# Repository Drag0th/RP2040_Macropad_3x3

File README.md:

# RP2040_Macropad_3x3
RP2040_Macropad_3x3 is a compact macropad project designed as a customizable USB input device for productivity and control tasks. It provides a 3×3 key layout combined with three rotary encoders and an integrated display, allowing users to trigger shortcuts, control values, and receive visual feedback in real time. The device is intended for use cases such as workflow automation, media control, creative software, or development environments. Overall, the project serves as a flexible platform for building a dedicated control pad tailored to specific user needs.

# :floppy_disk: Firmware
The RP2040_Macropad_3x3 uses [**QMK firmware**](https://github.com/qmk) as its dedicated software platform, allowing full customization of keys, rotary encoders, and the integrated display. This enables users to configure the macropad for shortcuts, macros, and workflow-specific controls.

# :file_folder: References, Links and Notes
- [RP2040 Datasheet](https://github.com/Drag0th/RP2040_Macropad_3x3/blob/main/Documentation/RP-008371-DS-1-rp2040-datasheet.pdf)
- [W25Q16JV Datasheet](https://github.com/Drag0th/RP2040_Macropad_3x3/blob/main/Documentation/w25q16jv%20spi%20revg%2003222018%20plus.pdf)

# :page_facing_up: License
*All hardware designs are released under the CERN-OHL-P v2 license.*

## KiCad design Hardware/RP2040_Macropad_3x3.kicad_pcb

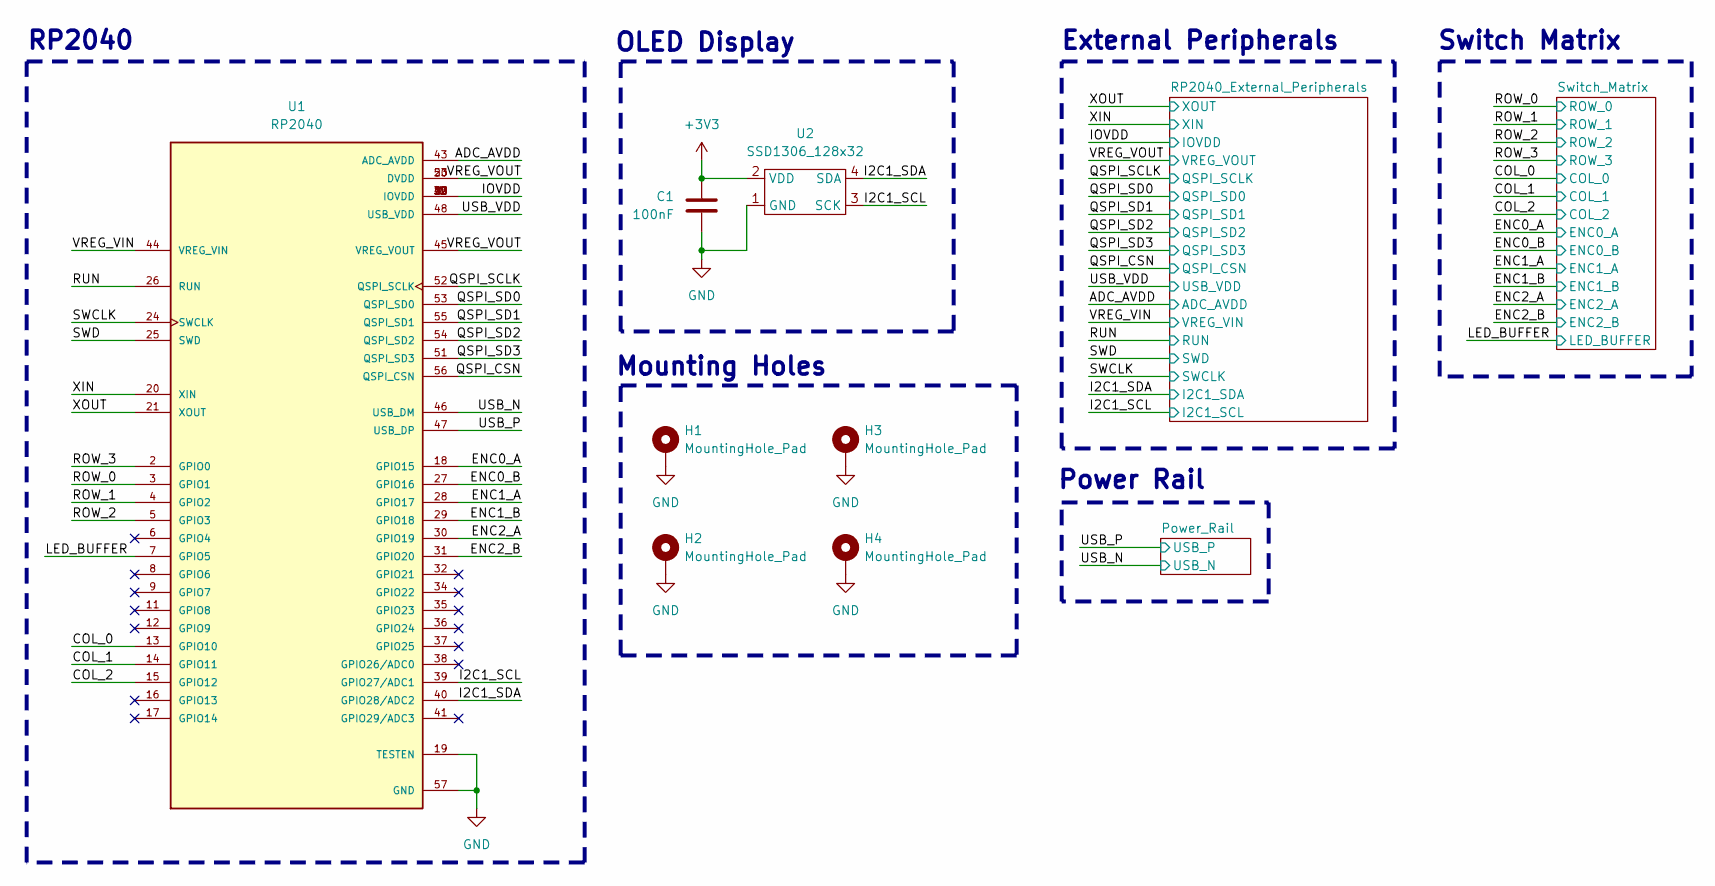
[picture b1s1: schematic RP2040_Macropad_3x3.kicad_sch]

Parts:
C1: 100nF; C_0603_1608Metric_Pad1.08x0.95mm_HandSolder
H1, H2, H3, H4: MountingHole_Pad; MountingHole_3.2mm_M3_Pad
U1: RP2040; QFN40P700X700X90-57N; PARTREV 1.6.1
U2: SSD1306_128x32; SSD1306_128x32_Display_Module

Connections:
+3V3: C1.2, U1.1 (IOVDD), U1.10 (IOVDD), U1.22 (IOVDD), U1.33 (IOVDD), U1.42 (IOVDD), U1.44 (VREG_VIN), U1.48 (USB_VDD), U1.49 (IOVDD), U2.2 (VDD); also elsewhere on the board
/ADC_AVDD: U1.43 (ADC_AVDD); also elsewhere on the board
/COL_0: U1.13 (GPIO10); also elsewhere on the board
/COL_1: U1.14 (GPIO11); also elsewhere on the board
/COL_2: U1.15 (GPIO12); also elsewhere on the board
/ENC0_A: U1.18 (GPIO15); also elsewhere on the board
/ENC0_B: U1.27 (GPIO16); also elsewhere on the board
/ENC1_A: U1.28 (GPIO17); also elsewhere on the board
/ENC1_B: U1.29 (GPIO18); also elsewhere on the board
/ENC2_A: U1.30 (GPIO19); also elsewhere on the board
/ENC2_B: U1.31 (GPIO20); also elsewhere on the board
/I2C1_SCL: U1.39 (GPIO27/ADC1), U2.3 (SCK); also elsewhere on the board
/I2C1_SDA: U1.40 (GPIO28/ADC2), U2.4 (SDA); also elsewhere on the board
/LED_BUFFER: U1.7 (GPIO5); also elsewhere on the board
/QSPI_CSN: U1.56 (QSPI_CSN); also elsewhere on the board
/QSPI_SCLK: U1.52 (QSPI_SCLK); also elsewhere on the board
/QSPI_SD0: U1.53 (QSPI_SD0); also elsewhere on the board
/QSPI_SD1: U1.55 (QSPI_SD1); also elsewhere on the board
/QSPI_SD2: U1.54 (QSPI_SD2); also elsewhere on the board
/QSPI_SD3: U1.51 (QSPI_SD3); also elsewhere on the board
/ROW_0: U1.3 (GPIO1); also elsewhere on the board
/ROW_1: U1.4 (GPIO2); also elsewhere on the board
/ROW_2: U1.5 (GPIO3); also elsewhere on the board
/ROW_3: U1.2 (GPIO0); also elsewhere on the board
/RUN: U1.26 (RUN); also elsewhere on the board
/SWCLK: U1.24 (SWCLK); also elsewhere on the board
/SWD: U1.25 (SWD); also elsewhere on the board
/USB_N: U1.46 (USB_DM); also elsewhere on the board
/USB_P: U1.47 (USB_DP); also elsewhere on the board
/VREG_VOUT: U1.23 (DVDD), U1.45 (VREG_VOUT), U1.50 (DVDD); also elsewhere on the board
/XIN: U1.20 (XIN); also elsewhere on the board
/XOUT: U1.21 (XOUT); also elsewhere on the board
GND: C1.1, H1.1, H2.1, H3.1, H4.1, U1.19 (TESTEN), U1.57 (GND), U2.1 (GND); also elsewhere on the board

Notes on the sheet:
OLED Display
RP2040
External Peripherals
Switch Matrix
Mounting Holes
Power Rail

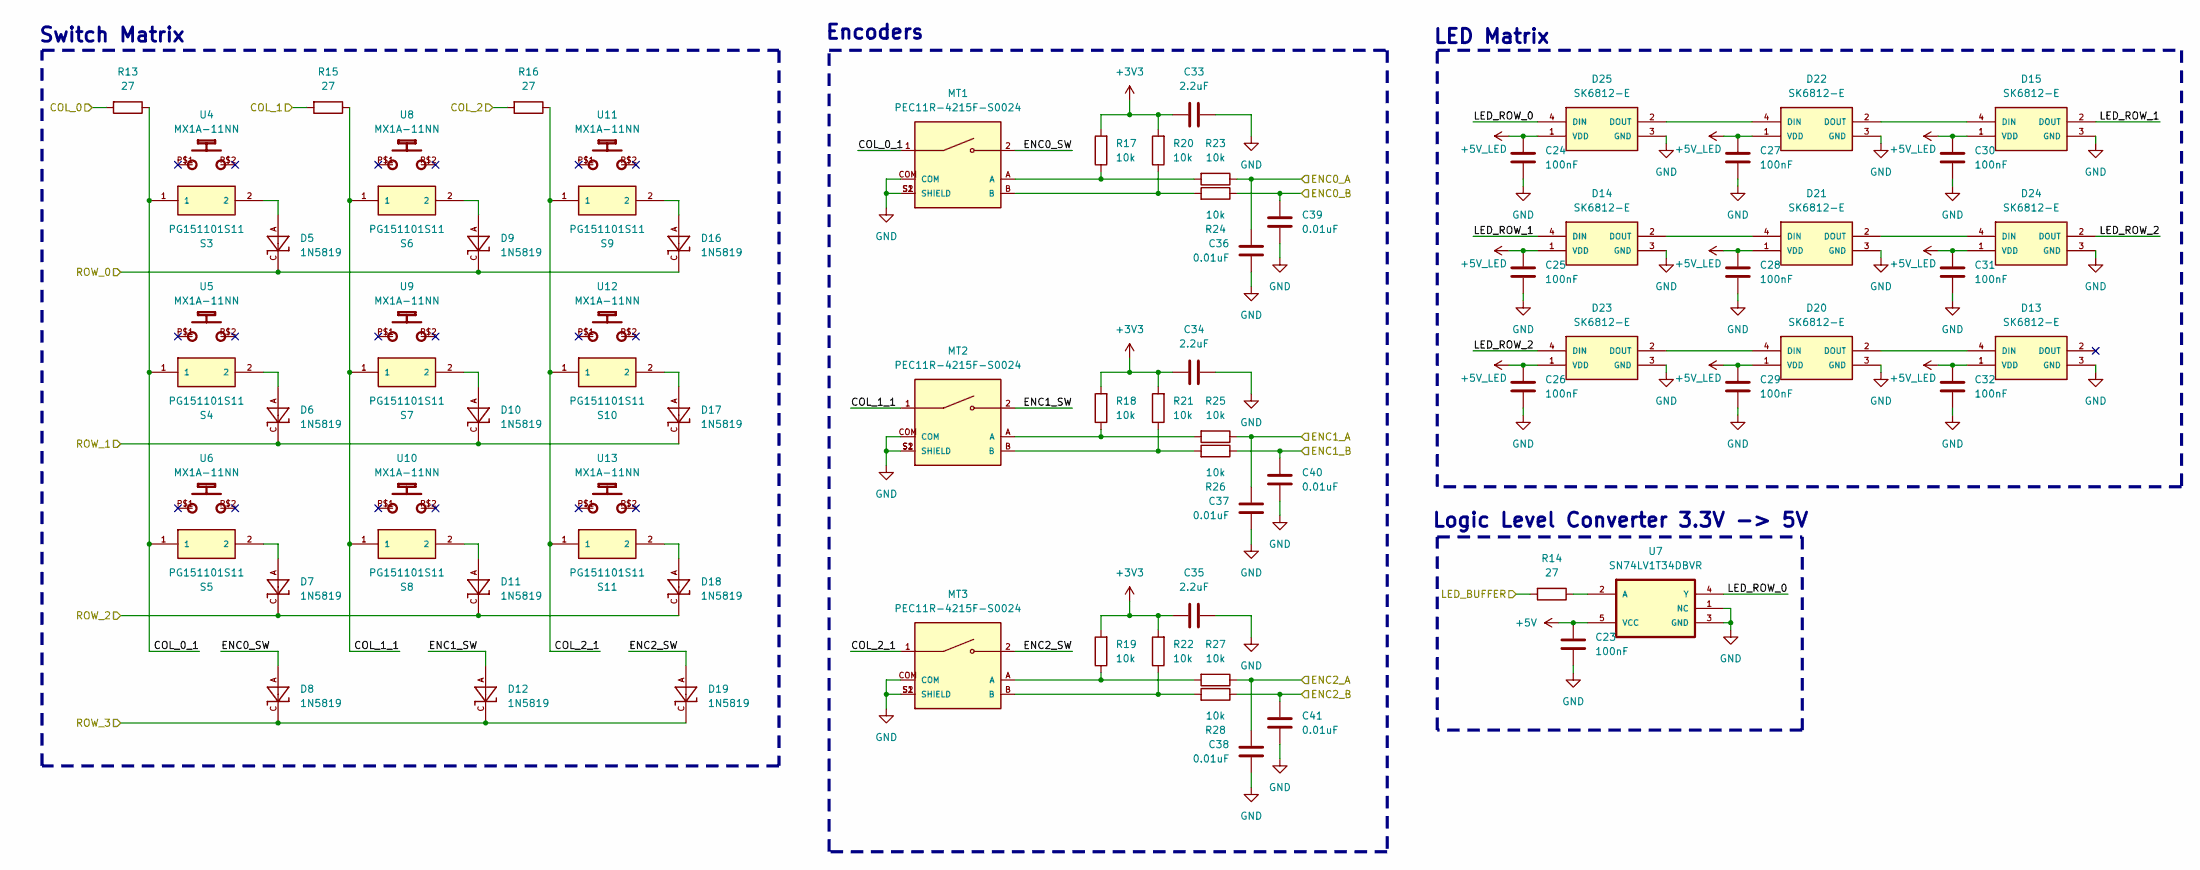
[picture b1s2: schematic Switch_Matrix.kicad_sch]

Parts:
C23, C24, C25, C26, C27, C28, C29, C30, C31, C32: 100nF; C_0603_1608Metric_Pad1.08x0.95mm_HandSolder
C33, C34, C35: 2.2uF; C_0603_1608Metric_Pad1.08x0.95mm_HandSolder
C36, C37, C38, C39, C40, C41: 0.01uF; C_0603_1608Metric_Pad1.08x0.95mm_HandSolder
D5, D6, D7, D8, D9, D10, D11, D12, D16, D17, D18, D19: 1N5819; SOD323
D13, D14, D15, D20, D21, D22, D23, D24, D25: SK6812-E; LED_SK6812-E; PARTREV 2
MT1, MT2, MT3: PEC11R-4215F-S0024; XDCR_PEC11R-4215F-S0024; PARTREV Rev. 09/19
R13, R14, R15, R16: 27; R_0603_1608Metric_Pad0.98x0.95mm_HandSolder
R17, R18, R19, R20, R21, R22, R23, R24, R25, R26, R27, R28: 10k; R_0603_1608Metric_Pad0.98x0.95mm_HandSolder
S3, S4, S5, S6, S7, S8, S9, S10, S11: PG151101S11; SW_PG151101S11; PARTREV A
U4, U5, U6, U8, U9, U10, U11, U12, U13: MX1A-11NN; CHERRY_MX1A-11NN_SWITCH
U7: SN74LV1T34DBVR; SOT95P280X145-5N

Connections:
+3V3: C33.2, C34.2, C35.2, R17.2, R18.2, R19.2, R20.2, R21.2, R22.2; also elsewhere on the board
+5V: C23.2, U7.5 (VCC); also elsewhere on the board
+5V_LED: C24.2, C25.2, C26.2, C27.2, C28.2, C29.2, C30.2, C31.2, C32.2, D13.1 (VDD), D14.1 (VDD), D15.1 (VDD), D20.1 (VDD), D21.1 (VDD), D22.1 (VDD), D23.1 (VDD), D24.1 (VDD), D25.1 (VDD); also elsewhere on the board
/COL_0: R13.2; also elsewhere on the board
/COL_1: R15.2; also elsewhere on the board
/COL_2: R16.2; also elsewhere on the board
/ENC0_A: C36.1, R23.1; also elsewhere on the board
/ENC0_B: C39.2, R24.1; also elsewhere on the board
/ENC1_A: C37.1, R25.1; also elsewhere on the board
/ENC1_B: C40.2, R26.1; also elsewhere on the board
/ENC2_A: C38.1, R27.1; also elsewhere on the board
/ENC2_B: C41.2, R28.1; also elsewhere on the board
/LED_BUFFER: R14.2; also elsewhere on the board
/ROW_0: D5.C, D9.C, D16.C; also elsewhere on the board
/ROW_1: D6.C, D10.C, D17.C; also elsewhere on the board
/ROW_2: D7.C, D11.C, D18.C; also elsewhere on the board
/ROW_3: D8.C, D12.C, D19.C; also elsewhere on the board
/Switch_Matrix/COL_0_1: MT1.1, R13.1, S3.1, S4.1, S5.1
/Switch_Matrix/COL_1_1: MT2.1, R15.1, S6.1, S7.1, S8.1
/Switch_Matrix/COL_2_1: MT3.1, R16.1, S9.1, S10.1, S11.1
/Switch_Matrix/ENC0_SW: D8.A, MT1.2
/Switch_Matrix/ENC1_SW: D12.A, MT2.2
/Switch_Matrix/ENC2_SW: D19.A, MT3.2
/Switch_Matrix/LED_ROW_0: D25.4 (DIN), U7.4 (Y)
/Switch_Matrix/LED_ROW_1: D14.4 (DIN), D15.2 (DOUT)
/Switch_Matrix/LED_ROW_2: D23.4 (DIN), D24.2 (DOUT)
GND: C23.1, C24.1, C25.1, C26.1, C27.1, C28.1, C29.1, C30.1, C31.1, C32.1, C33.1, C34.1, C35.1, C36.2, C37.2, C38.2, C39.1, C40.1, C41.1, D13.3 (GND), D14.3 (GND), D15.3 (GND), D20.3 (GND), D21.3 (GND), D22.3 (GND), D23.3 (GND), D24.3 (GND), D25.3 (GND), MT1.COM, MT1.S1 (SHIELD), MT1.S2 (SHIELD), MT2.COM, MT2.S1 (SHIELD), MT2.S2 (SHIELD), MT3.COM, MT3.S1 (SHIELD), MT3.S2 (SHIELD), U7.1 (NC), U7.3 (GND); also elsewhere on the board
unnamed: D5.A, S3.2
unnamed: D6.A, S4.2
unnamed: D7.A, S5.2
unnamed: D9.A, S6.2
unnamed: D10.A, S7.2
unnamed: D11.A, S8.2
unnamed: D13.4 (DIN), D20.2 (DOUT)
unnamed: D14.2 (DOUT), D21.4 (DIN)
unnamed: D15.4 (DIN), D22.2 (DOUT)
unnamed: D16.A, S9.2
unnamed: D17.A, S10.2
unnamed: D18.A, S11.2
unnamed: D20.4 (DIN), D23.2 (DOUT)
unnamed: D21.2 (DOUT), D24.4 (DIN)
unnamed: D22.4 (DIN), D25.2 (DOUT)
unnamed: MT1.A, R17.1, R23.2
unnamed: MT1.B, R20.1, R24.2
unnamed: MT2.A, R18.1, R25.2
unnamed: MT2.B, R21.1, R26.2
unnamed: MT3.A, R19.1, R27.2
unnamed: MT3.B, R22.1, R28.2
unnamed: R14.1, U7.2 (A)

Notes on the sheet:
Encoders
Switch Matrix
Logic Level Converter 3.3V -> 5V
LED Matrix

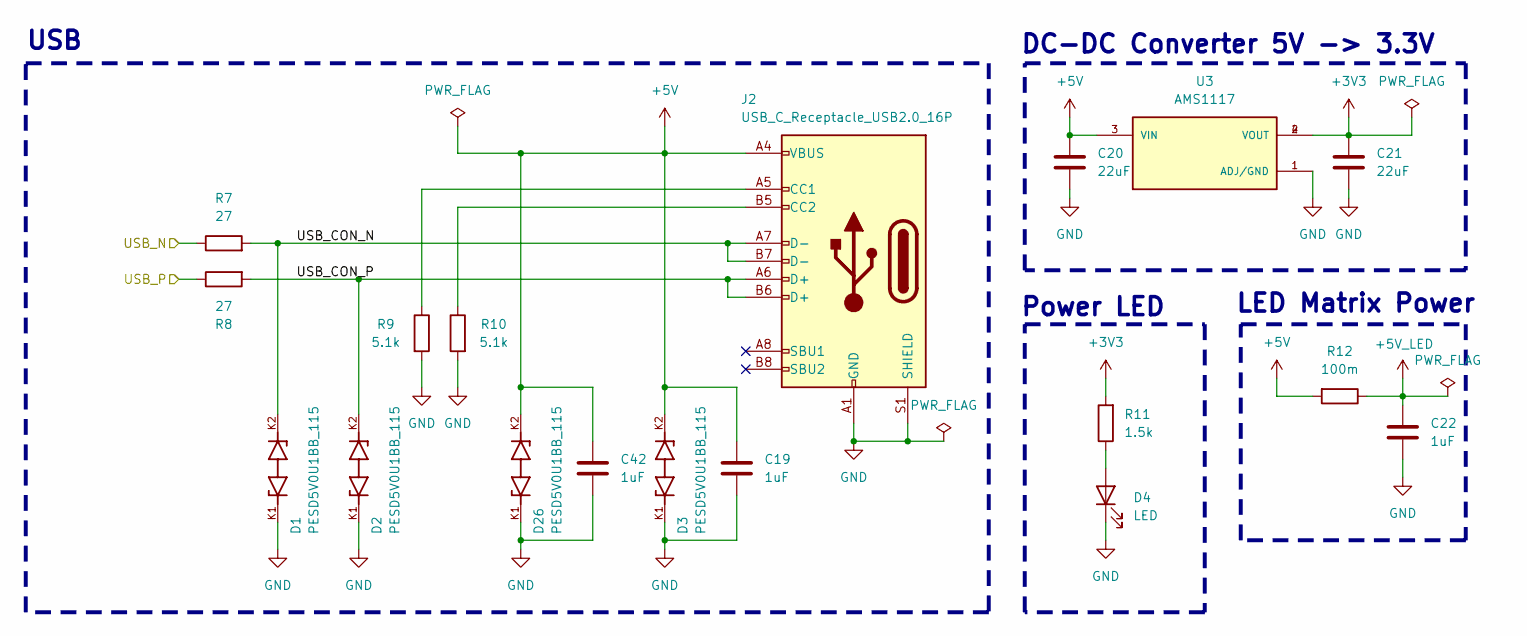
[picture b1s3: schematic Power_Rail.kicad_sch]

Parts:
C19, C22, C42: 1uF; C_0603_1608Metric_Pad1.08x0.95mm_HandSolder
C20, C21: 22uF; C_0603_1608Metric_Pad1.08x0.95mm_HandSolder
D1, D2, D3, D26: PESD5V0U1BB_115; DIO_PESD5V0U1BB_115; PARTREV 2
D4: LED; LED_0603_1608Metric_Pad1.05x0.95mm_HandSolder
J2: USB_C_Receptacle_USB2.0_16P; USB_C_Receptacle_HRO_TYPE-C-31-M-12
R7, R8: 27; R_0603_1608Metric_Pad0.98x0.95mm_HandSolder
R9, R10: 5.1k; R_0603_1608Metric_Pad0.98x0.95mm_HandSolder
R11: 1.5k; R_0603_1608Metric_Pad0.98x0.95mm_HandSolder
R12: 100m; R_1206_3216Metric_Pad1.30x1.75mm_HandSolder
U3: AMS1117; SOT229P700X180-4N; PARTREV N/A

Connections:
+3V3: C21.1, R11.2, U3.2 (VOUT), U3.4 (VOUT); also elsewhere on the board
+5V: C19.1, C20.1, C42.1, D3.K2, D26.K2, J2.A4 (VBUS), J2.A9 (VBUS), J2.B4 (VBUS), J2.B9 (VBUS), R12.2, U3.3 (VIN); also elsewhere on the board
+5V_LED: C22.1, R12.1; also elsewhere on the board
/Power_Rail/USB_CON_N: D1.K2, J2.A7 (D-), J2.B7 (D-), R7.2
/Power_Rail/USB_CON_P: D2.K2, J2.A6 (D+), J2.B6 (D+), R8.2
/USB_N: R7.1; also elsewhere on the board
/USB_P: R8.1; also elsewhere on the board
GND: C19.2, C20.2, C21.2, C22.2, C42.2, D1.K1, D2.K1, D3.K1, D4.1 (K), D26.K1, J2.A1 (GND), J2.A12 (GND), J2.B1 (GND), J2.B12 (GND), J2.S1 (SHIELD), R9.2, R10.2, U3.1 (ADJ/GND); also elsewhere on the board
unnamed: D4.2 (A), R11.1
unnamed: J2.A5 (CC1), R9.1
unnamed: J2.B5 (CC2), R10.1

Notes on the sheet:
USB
Power LED
DC-DC Converter 5V -> 3.3V
LED Matrix Power

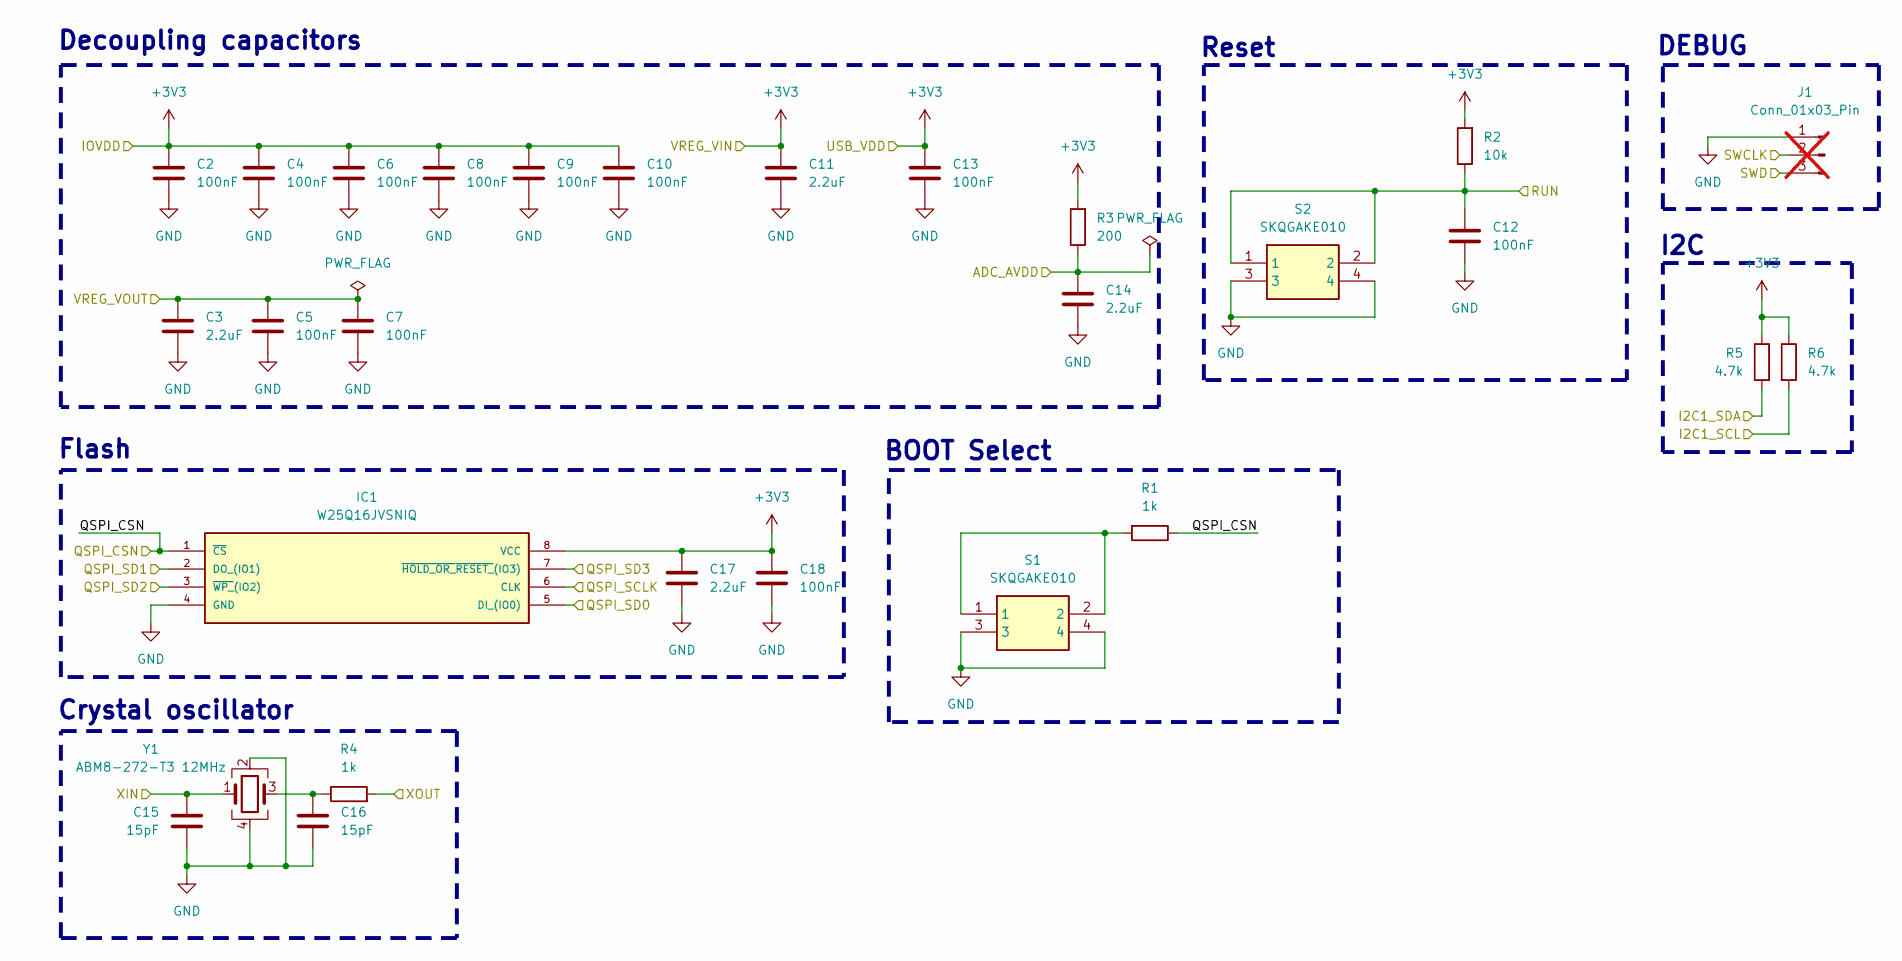
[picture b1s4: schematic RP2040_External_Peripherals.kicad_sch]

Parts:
C2, C4, C5, C6, C7, C8, C9, C10, C12, C13, C18: 100nF; C_0603_1608Metric_Pad1.08x0.95mm_HandSolder
C3, C11, C14, C17: 2.2uF; C_0603_1608Metric_Pad1.08x0.95mm_HandSolder
C15, C16: 15pF; C_0603_1608Metric_Pad1.08x0.95mm_HandSolder
IC1: W25Q16JVSNIQ; SOIC127P600X175-8N; MOUSER_PART_NUMBER 454-W25Q16JVSNIQ
J1: Conn_01x03_Pin; PinHeader_1x03_P2.54mm_Vertical; not fitted
R1, R4: 1k; R_0603_1608Metric_Pad0.98x0.95mm_HandSolder
R2: 10k; R_0603_1608Metric_Pad0.98x0.95mm_HandSolder
R3: 200; R_0603_1608Metric_Pad0.98x0.95mm_HandSolder
R5, R6: 4.7k; R_0603_1608Metric_Pad0.98x0.95mm_HandSolder
S1, S2: SKQGAKE010; Mouser Part Number 688-SKQGAKE010
Y1: ABM8-272-T3 12MHz; Crystal_SMD_3225-4Pin_3.2x2.5mm_HandSoldering

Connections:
+3V3: C2.1, C4.1, C6.1, C8.1, C9.1, C10.1, C11.1, C13.1, C17.1, C18.1, IC1.8 (VCC), R2.2, R3.2, R5.1, R6.1; also elsewhere on the board
/ADC_AVDD: C14.1, R3.1; also elsewhere on the board
/I2C1_SCL: R6.2; also elsewhere on the board
/I2C1_SDA: R5.2; also elsewhere on the board
/QSPI_CSN: IC1.1 (~CS), R1.1; also elsewhere on the board
/QSPI_SCLK: IC1.6 (CLK); also elsewhere on the board
/QSPI_SD0: IC1.5 (DI_(IO0)); also elsewhere on the board
/QSPI_SD1: IC1.2 (DO_(IO1)); also elsewhere on the board
/QSPI_SD2: IC1.3 (~WP_(IO2)); also elsewhere on the board
/QSPI_SD3: IC1.7 (~HOLD_OR_~RESET_(IO3)); also elsewhere on the board
/RUN: C12.1, R2.1, S2.1, S2.2; also elsewhere on the board
/SWCLK: J1.2; also elsewhere on the board
/SWD: J1.3; also elsewhere on the board
/VREG_VOUT: C3.1, C5.1, C7.1; also elsewhere on the board
/XIN: C15.1, Y1.1; also elsewhere on the board
/XOUT: R4.2; also elsewhere on the board
GND: C2.2, C3.2, C4.2, C5.2, C6.2, C7.2, C8.2, C9.2, C10.2, C11.2, C12.2, C13.2, C14.2, C15.2, C16.2, C17.2, C18.2, IC1.4 (GND), J1.1, S1.3, S1.4, S2.3, S2.4, Y1.2, Y1.4; also elsewhere on the board
unnamed: C16.1, R4.1, Y1.3
unnamed: R1.2, S1.1, S1.2

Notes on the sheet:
Crystal oscillator
DEBUG
Decoupling capacitors
BOOT Select
I2C
Reset
Flash

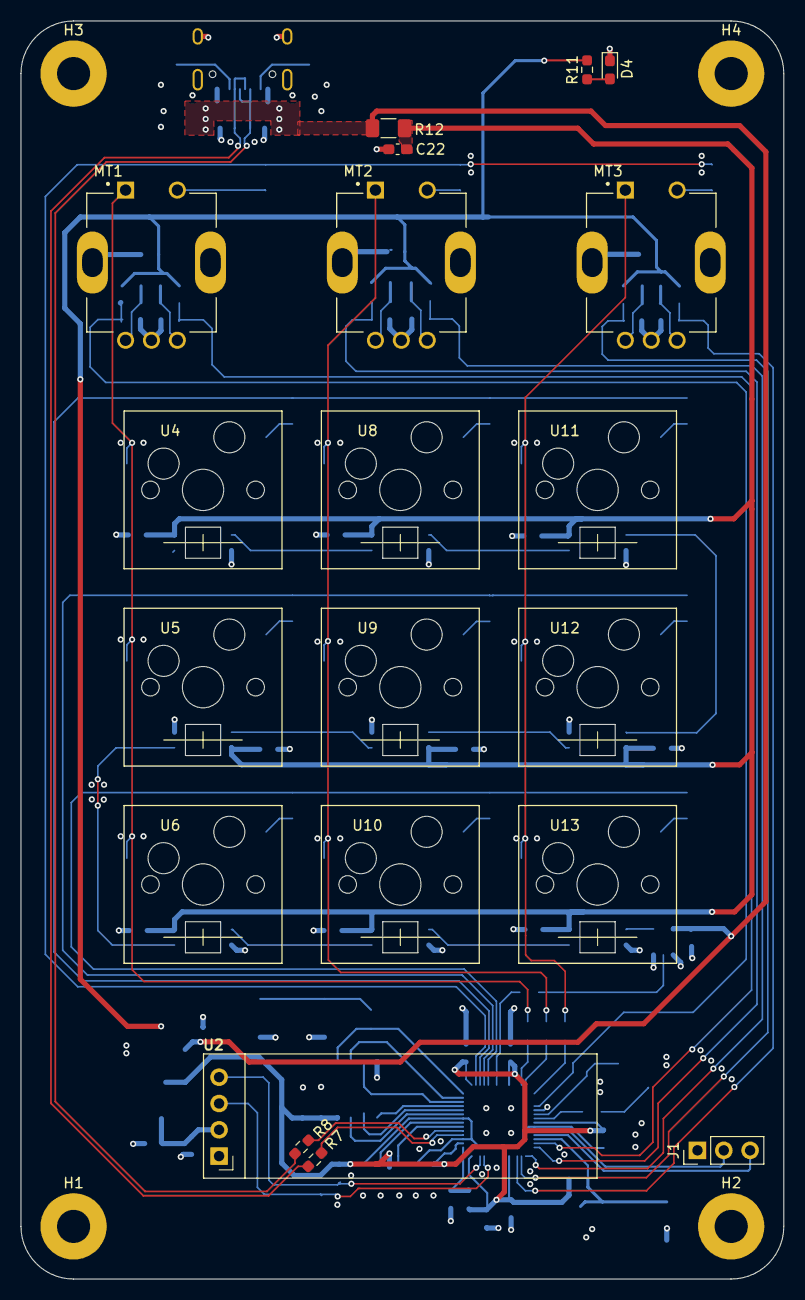
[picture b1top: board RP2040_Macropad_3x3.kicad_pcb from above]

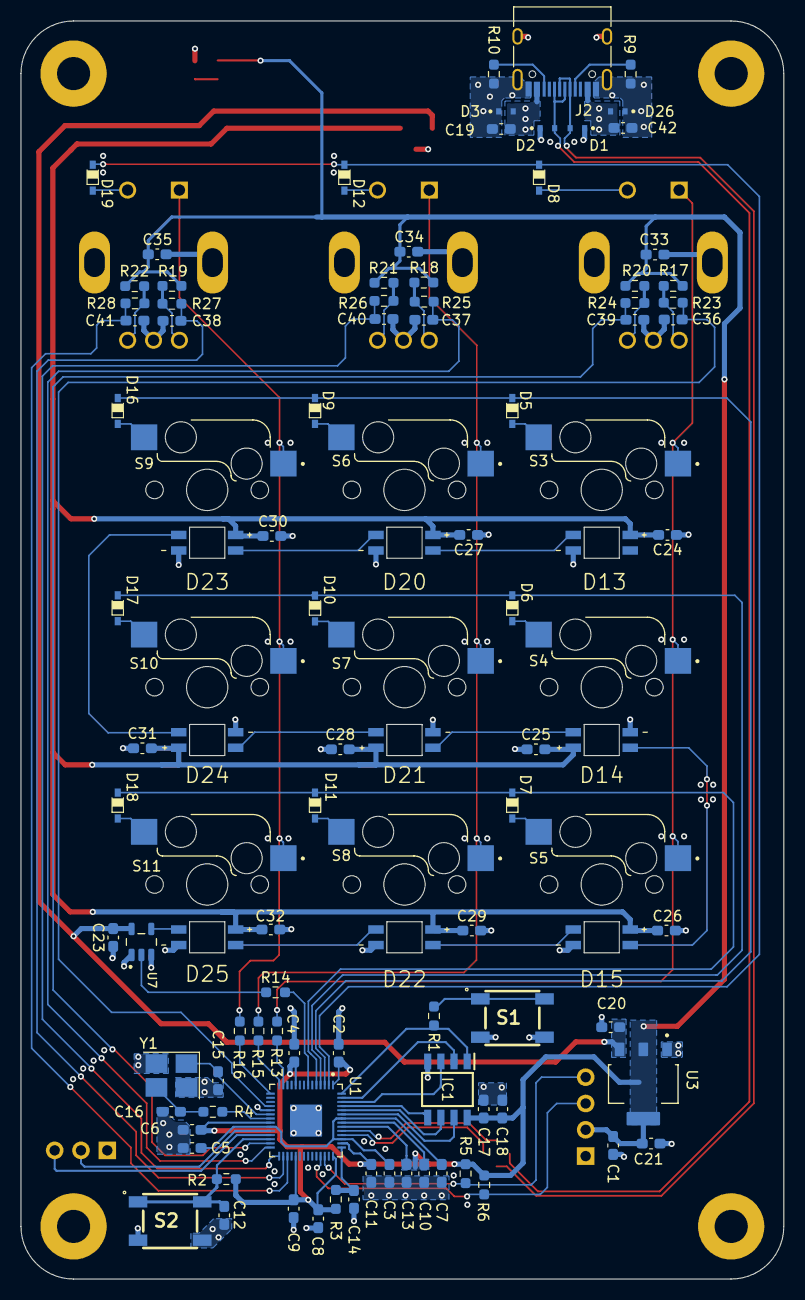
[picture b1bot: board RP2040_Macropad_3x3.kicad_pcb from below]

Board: 4 copper layers, 73.7 x 121.5 mm, 131 parts (107 on the bottom side), 73 nets.

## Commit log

2025-09-03 Clean Up
2025-09-04 USB, FLASH & Power Rail Update
2025-09-13 Schematic Update
2025-09-14 Schematic Clean Up
2025-09-14 PCB Update
2025-09-22 Layout Update
2026-01-13 Repo Cleanup
2026-01-13 Create LICENSE
